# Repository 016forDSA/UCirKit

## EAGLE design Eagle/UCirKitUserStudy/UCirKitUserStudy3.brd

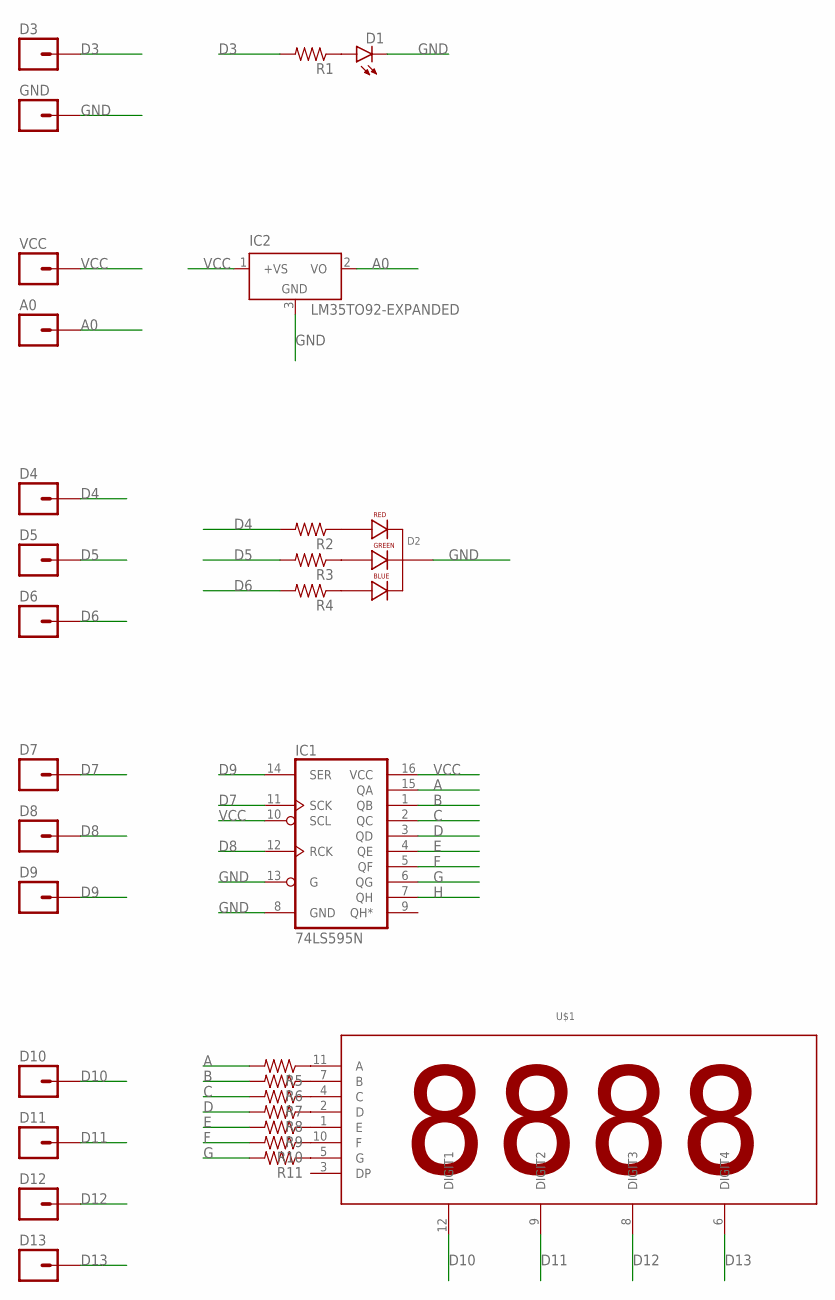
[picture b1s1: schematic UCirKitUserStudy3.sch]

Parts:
A0: M01PTH; 1X01
D1: LEDLED3MM-EXPANDED; LED3MM-EXPANDED
D2: LED-RGB-CC-THRUEXPANDED; LED-RGB-THRU-EXPANDED
D3, D4, D5, D6, D7, D8, D9, D10, D11, D12, D13: M01PTH; 1X01
GND: M01PTH; 1X01
IC1: 74LS595N; DIL16
IC2: LM35TO92-EXPANDED; TO92-EXPANDED
R1, R2, R3, R4, R5, R6, R7, R8, R9, R10, R11: 1KOHM-1/4W-1%(PTH)PTH-EXPANDED; PTH-EXPANDED
U$1: 4DIGIT_SEVEN_SEGMENT4DIGIT_SEVEN_SEGMENT; 4DIGIT_SEVEN_SEGMENT
VCC: M01PTH; 1X01

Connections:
A: IC1.15 (QA), R5.P$2 (2)
A0: A0.1, IC2.2 (VO)
B: IC1.1 (QB), R6.P$2 (2)
C: IC1.2 (QC), R7.P$2 (2)
D: IC1.3 (QD), R8.P$2 (2)
D3: D3.1, R1.P$2 (2)
D4: D4.1, R2.P$2 (2)
D5: D5.1, R3.P$2 (2)
D6: D6.1, R4.P$2 (2)
D7: D7.1, IC1.11 (SCK)
D8: D8.1, IC1.12 (RCK)
D9: D9.1, IC1.14 (SER)
D10: D10.1, U$1.12 (DIGIT1)
D11: D11.1, U$1.9 (DIGIT2)
D12: D12.1, U$1.8 (DIGIT3)
D13: D13.1, U$1.6 (DIGIT4)
E: IC1.4 (QE), R9.P$2 (2)
F: IC1.5 (QF), R10.P$2 (2)
G: IC1.6 (QG), R11.P$2 (2)
GND: D1.K (C), D2.2 (CATHODE), GND.1, IC1.8 (GND), IC1.13 (G), IC2.3 (GND)
H: IC1.7 (QH)
unnamed: D1.A, R1.P$1 (1)
unnamed: D2.1 (RED_CATHODE), R2.P$1 (1)
unnamed: D2.3 (GREEN_CATHODE), R3.P$1 (1)
unnamed: D2.4 (BLUE_CATHODE), R4.P$1 (1)
unnamed: R5.P$1 (1), U$1.11 (A)
unnamed: R6.P$1 (1), U$1.7 (B)
unnamed: R7.P$1 (1), U$1.4 (C)
unnamed: R8.P$1 (1), U$1.2 (D)
unnamed: R9.P$1 (1), U$1.1 (E)
unnamed: R10.P$1 (1), U$1.10 (F)
unnamed: R11.P$1 (1), U$1.5 (G)
VCC: IC1.10 (SCL), IC1.16 (VCC), IC2.1 (+VS), VCC.1

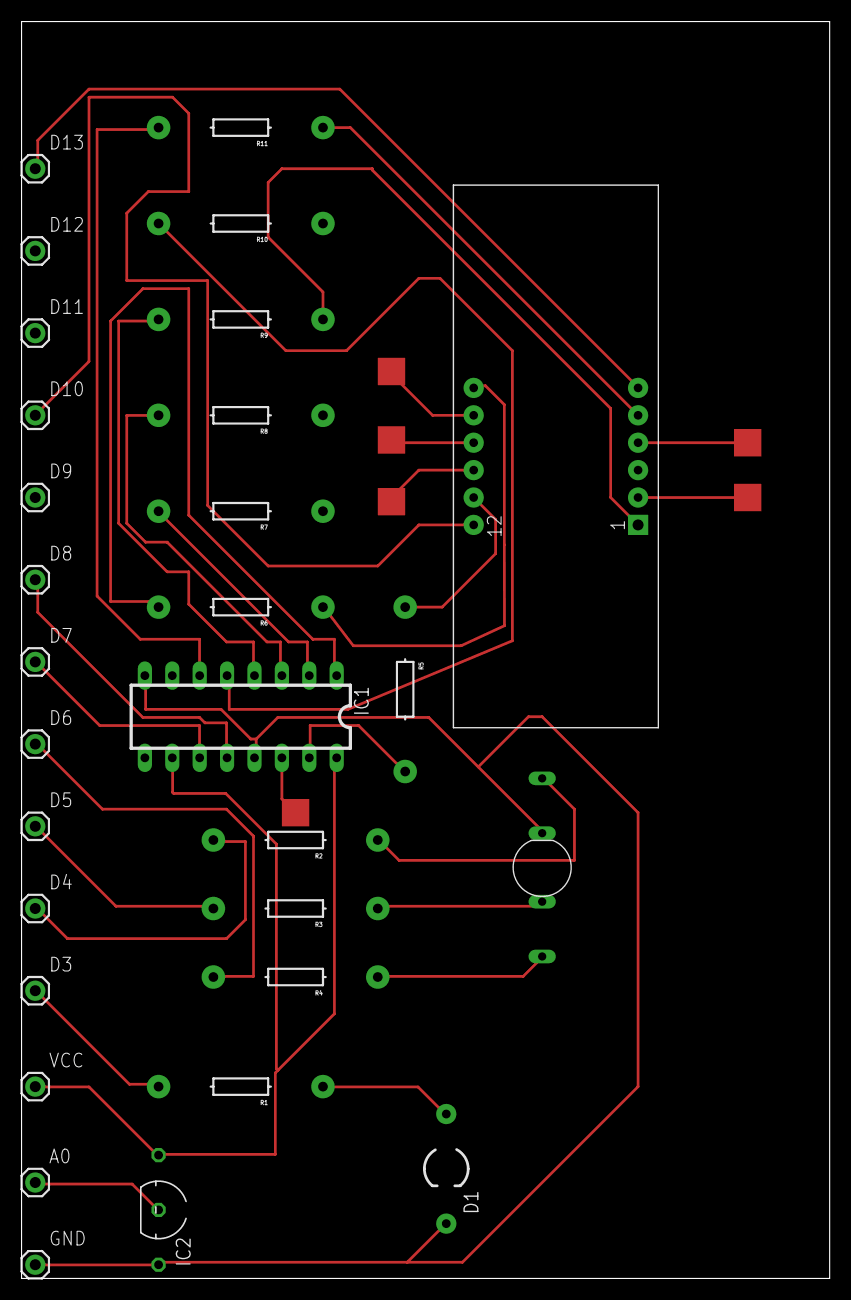
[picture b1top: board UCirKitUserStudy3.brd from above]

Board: 2 copper layers, 74.9 x 116.5 mm, 30 parts (0 on the bottom side), 32 nets.

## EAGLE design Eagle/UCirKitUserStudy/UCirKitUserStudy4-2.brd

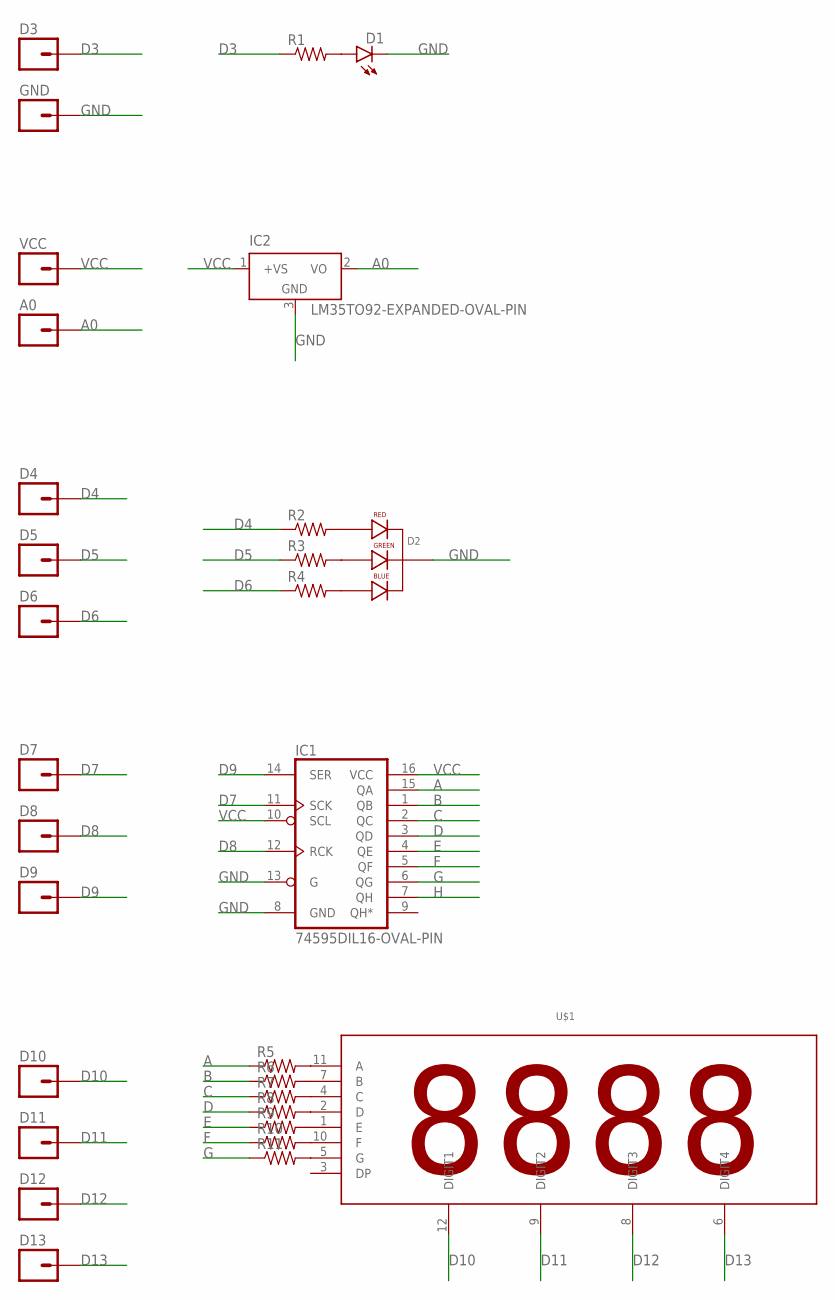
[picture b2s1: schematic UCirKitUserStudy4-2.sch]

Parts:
A0: M01OVAL_PIN; 1X01_OVAL_PIN
D1: LEDLED3MM-EXPANDED-OVAL-PIN; LED3MM-EXPANDED-OVAL-PIN
D2: LED-RGB-CC-THRULED-RGB-THRU-EXPANDED-OVAL-PIN; LED-RGB-THRU-EXPANDED-OVAL-PIN
D3, D4, D5, D6, D7, D8, D9, D10, D11, D12, D13: M01OVAL_PIN; 1X01_OVAL_PIN
GND: M01OVAL_PIN; 1X01_OVAL_PIN
IC1: 74595DIL16-OVAL-PIN; DIL16-OVAL-PIN
IC2: LM35TO92-EXPANDED-OVAL-PIN; TO92-EXPANDED-OVAL-PIN
R1, R2, R3, R4, R5, R6, R7, R8, R9, R10, R11: 1KOHM-1/4W-1%(PTH)PTH-EXPANDED-OVAL-PIN; PTH-EXPANDED-OVAL-PIN
U$1: 4DIGIT_SEVEN_SEGMENT4DIGIT_SEVEN_SEGMENT_OVAL_PIN; 4DIGIT_SEVEN_SEGMENT_OVAL_PIN
VCC: M01OVAL_PIN; 1X01_OVAL_PIN

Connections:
A: IC1.15 (QA), R5.P$1 (1)
A0: A0.1, IC2.2 (VO)
B: IC1.1 (QB), R6.P$1 (1)
C: IC1.2 (QC), R7.P$1 (1)
D: IC1.3 (QD), R8.P$1 (1)
D3: D3.1, R1.P$1 (1)
D4: D4.1, R2.P$1 (1)
D5: D5.1, R3.P$1 (1)
D6: D6.1, R4.P$1 (1)
D7: D7.1, IC1.11 (SCK)
D8: D8.1, IC1.12 (RCK)
D9: D9.1, IC1.14 (SER)
D10: D10.1, U$1.12 (DIGIT1)
D11: D11.1, U$1.9 (DIGIT2)
D12: D12.1, U$1.8 (DIGIT3)
D13: D13.1, U$1.6 (DIGIT4)
E: IC1.4 (QE), R9.P$1 (1)
F: IC1.5 (QF), R10.P$1 (1)
G: IC1.6 (QG), R11.P$1 (1)
GND: D1.K (C), D2.2 (CATHODE), GND.1, IC1.8 (GND), IC1.13 (G), IC2.3 (GND)
H: IC1.7 (QH)
unnamed: D1.A, R1.P$2 (2)
unnamed: D2.1 (RED_CATHODE), R2.P$2 (2)
unnamed: D2.3 (GREEN_CATHODE), R3.P$2 (2)
unnamed: D2.4 (BLUE_CATHODE), R4.P$2 (2)
unnamed: R5.P$2 (2), U$1.11 (A)
unnamed: R6.P$2 (2), U$1.7 (B)
unnamed: R7.P$2 (2), U$1.4 (C)
unnamed: R8.P$2 (2), U$1.2 (D)
unnamed: R9.P$2 (2), U$1.1 (E)
unnamed: R10.P$2 (2), U$1.10 (F)
unnamed: R11.P$2 (2), U$1.5 (G)
VCC: IC1.10 (SCL), IC1.16 (VCC), IC2.1 (+VS), VCC.1

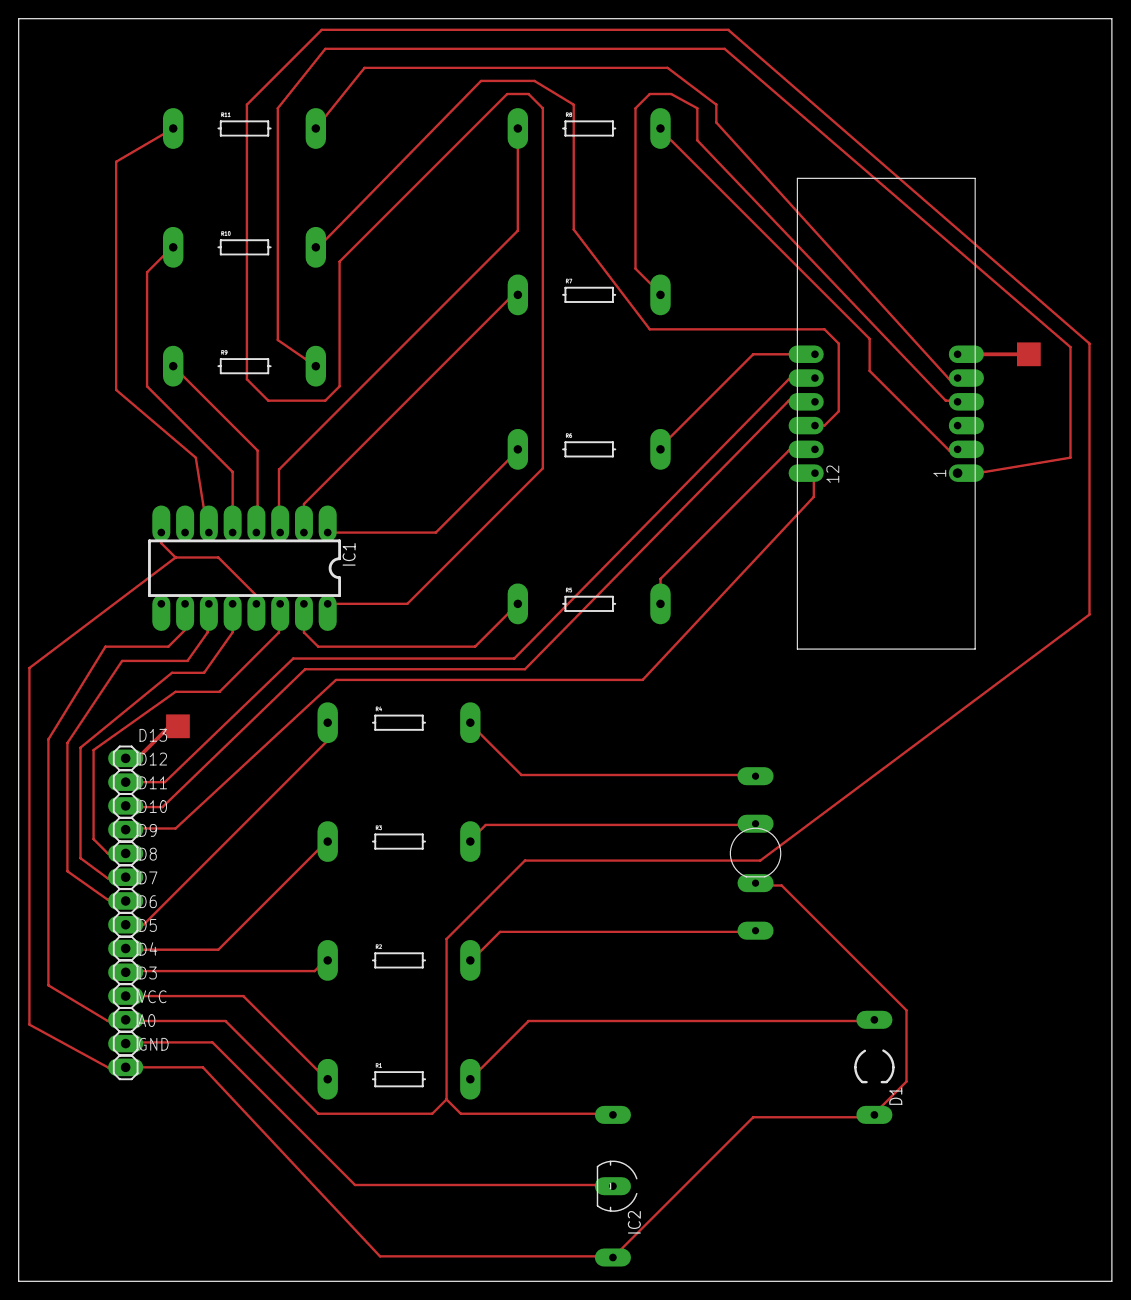
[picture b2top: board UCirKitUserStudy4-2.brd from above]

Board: 2 copper layers, 116.8 x 134.9 mm, 30 parts (0 on the bottom side), 32 nets.

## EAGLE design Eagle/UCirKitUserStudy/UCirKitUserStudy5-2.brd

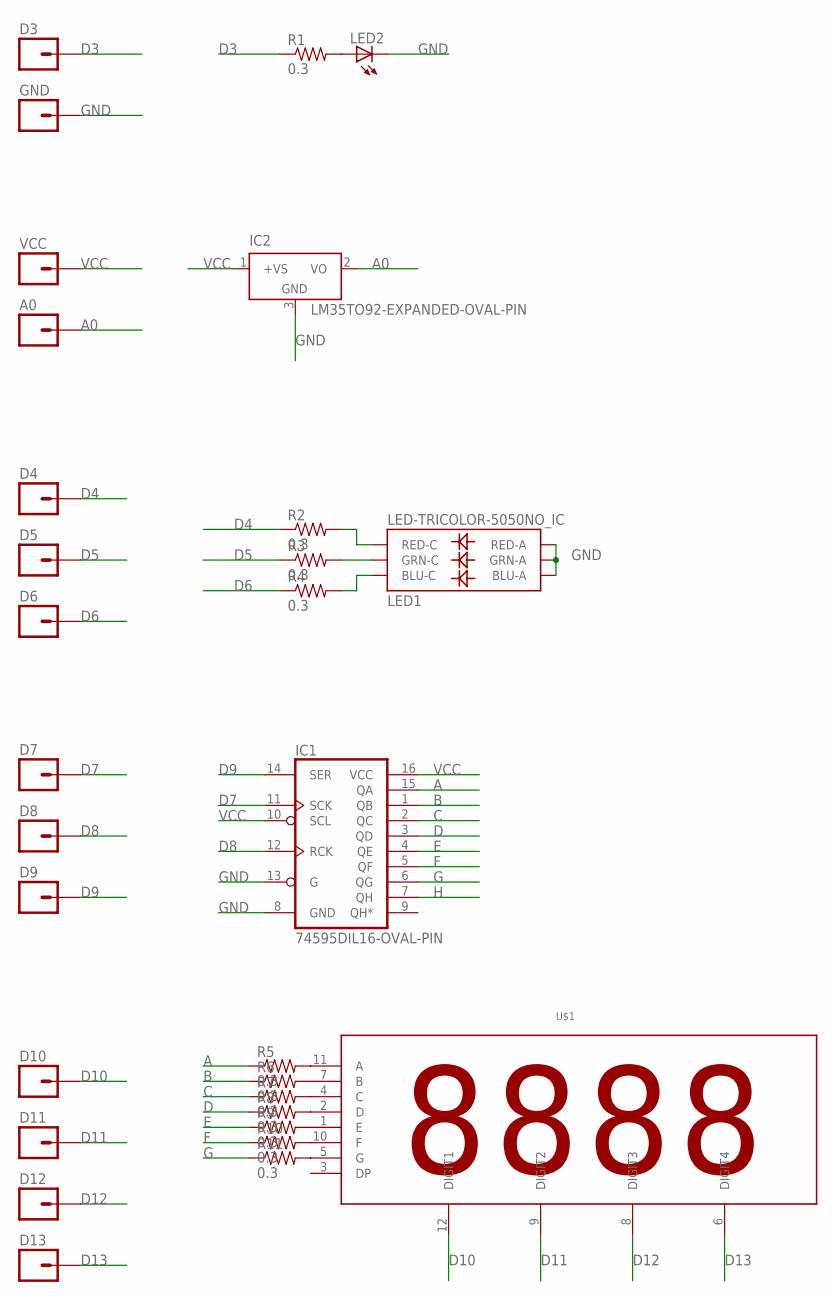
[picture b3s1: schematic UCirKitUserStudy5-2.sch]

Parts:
A0: M01OVAL_PIN; 1X01_OVAL_PIN
D3, D4, D5, D6, D7, D8, D9, D10, D11, D12, D13: M01OVAL_PIN; 1X01_OVAL_PIN
GND: M01OVAL_PIN; 1X01_OVAL_PIN
IC1: 74595DIL16-OVAL-PIN; DIL16-OVAL-PIN
IC2: LM35TO92-EXPANDED-OVAL-PIN; TO92-EXPANDED-OVAL-PIN
LED1: LED-TRICOLOR-5050NO_IC; LED-TRICOLOR-5050
LED2: LEDCHIP-LED0805; CHIP-LED0805
R1, R2, R3, R4, R5, R6, R7, R8, R9, R10, R11: 0.3; 0805
U$1: 4DIGIT_SEVEN_SEGMENT4DIGIT_SEVEN_SEGMENT_OVAL_PIN; 4DIGIT_SEVEN_SEGMENT_OVAL_PIN
VCC: M01OVAL_PIN; 1X01_OVAL_PIN

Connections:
A: IC1.15 (QA), R5.1
A0: A0.1, IC2.2 (VO)
B: IC1.1 (QB), R6.1
C: IC1.2 (QC), R7.1
D: IC1.3 (QD), R8.1
D3: D3.1, R1.1
D4: D4.1, R2.1
D5: D5.1, R3.1
D6: D6.1, R4.1
D7: D7.1, IC1.11 (SCK)
D8: D8.1, IC1.12 (RCK)
D9: D9.1, IC1.14 (SER)
D10: D10.1, U$1.12 (DIGIT1)
D11: D11.1, U$1.9 (DIGIT2)
D12: D12.1, U$1.8 (DIGIT3)
D13: D13.1, U$1.6 (DIGIT4)
E: IC1.4 (QE), R9.1
F: IC1.5 (QF), R10.1
G: IC1.6 (QG), R11.1
GND: GND.1, IC1.8 (GND), IC1.13 (G), IC2.3 (GND), LED1.1 (GRN-A), LED1.2 (RED-A), LED1.3 (BLU-A), LED2.C
H: IC1.7 (QH)
unnamed: R5.2, U$1.11 (A)
unnamed: R6.2, U$1.7 (B)
unnamed: R7.2, U$1.4 (C)
unnamed: R8.2, U$1.2 (D)
unnamed: R9.2, U$1.1 (E)
unnamed: R10.2, U$1.10 (F)
unnamed: R11.2, U$1.5 (G)
unnamed: LED1.5 (RED-C), R2.2
unnamed: LED1.6 (GRN-C), R3.2
unnamed: LED1.4 (BLU-C), R4.2
unnamed: LED2.A, R1.2
VCC: IC1.10 (SCL), IC1.16 (VCC), IC2.1 (+VS), VCC.1

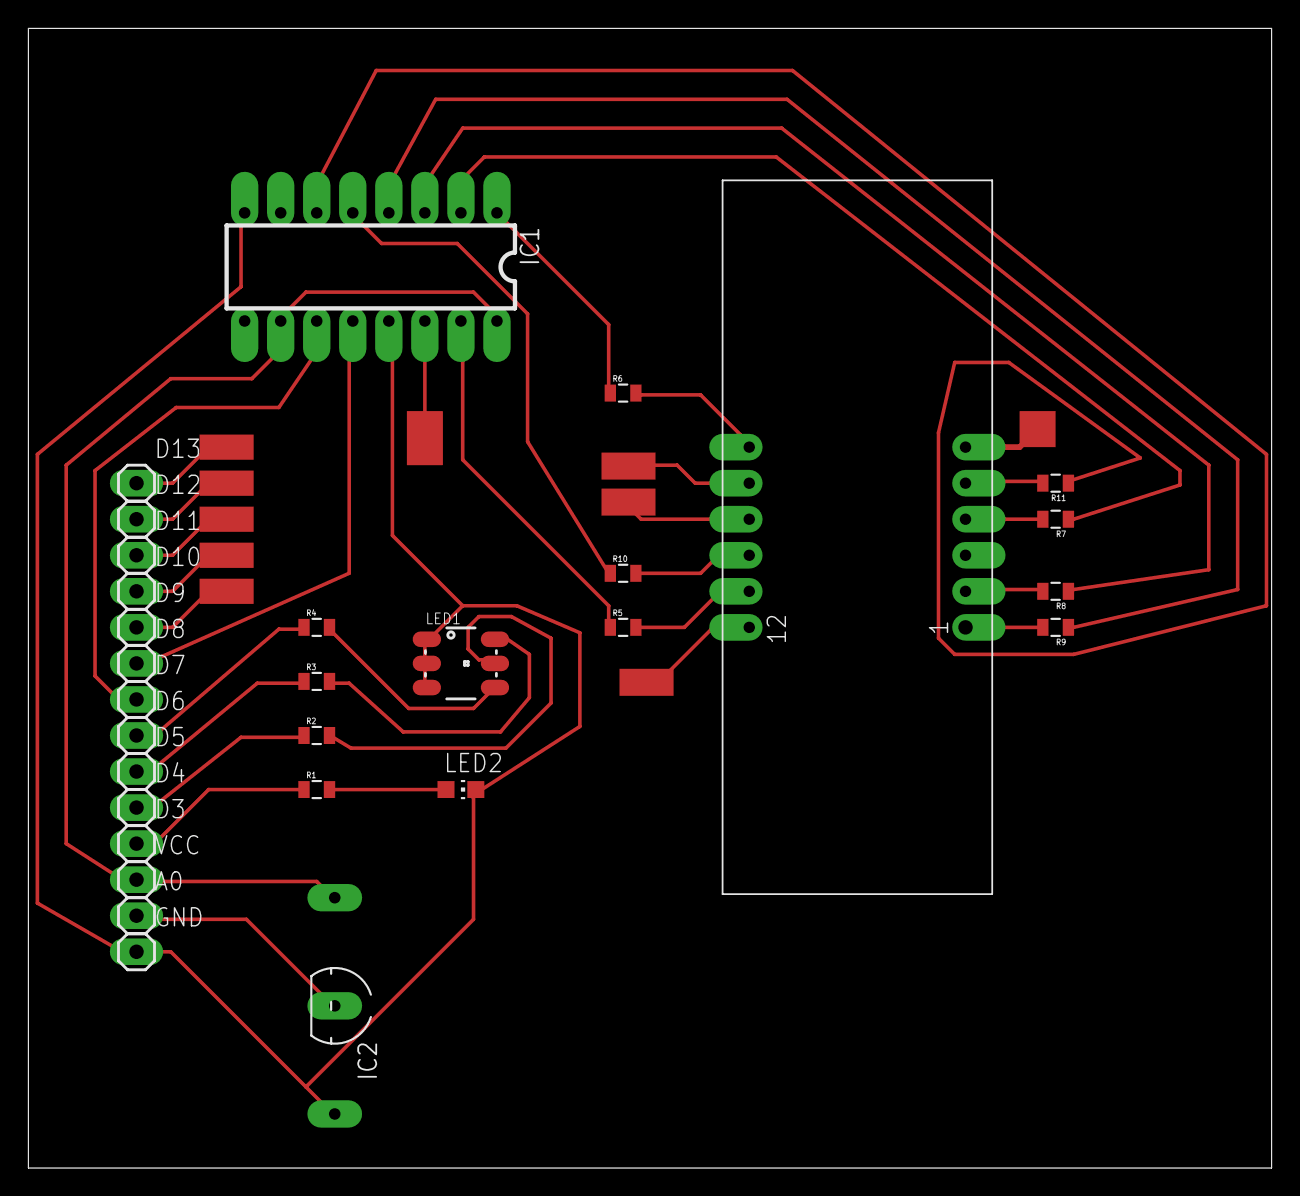
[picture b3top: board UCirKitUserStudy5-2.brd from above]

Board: 2 copper layers, 87.6 x 80.3 mm, 30 parts (0 on the bottom side), 32 nets.

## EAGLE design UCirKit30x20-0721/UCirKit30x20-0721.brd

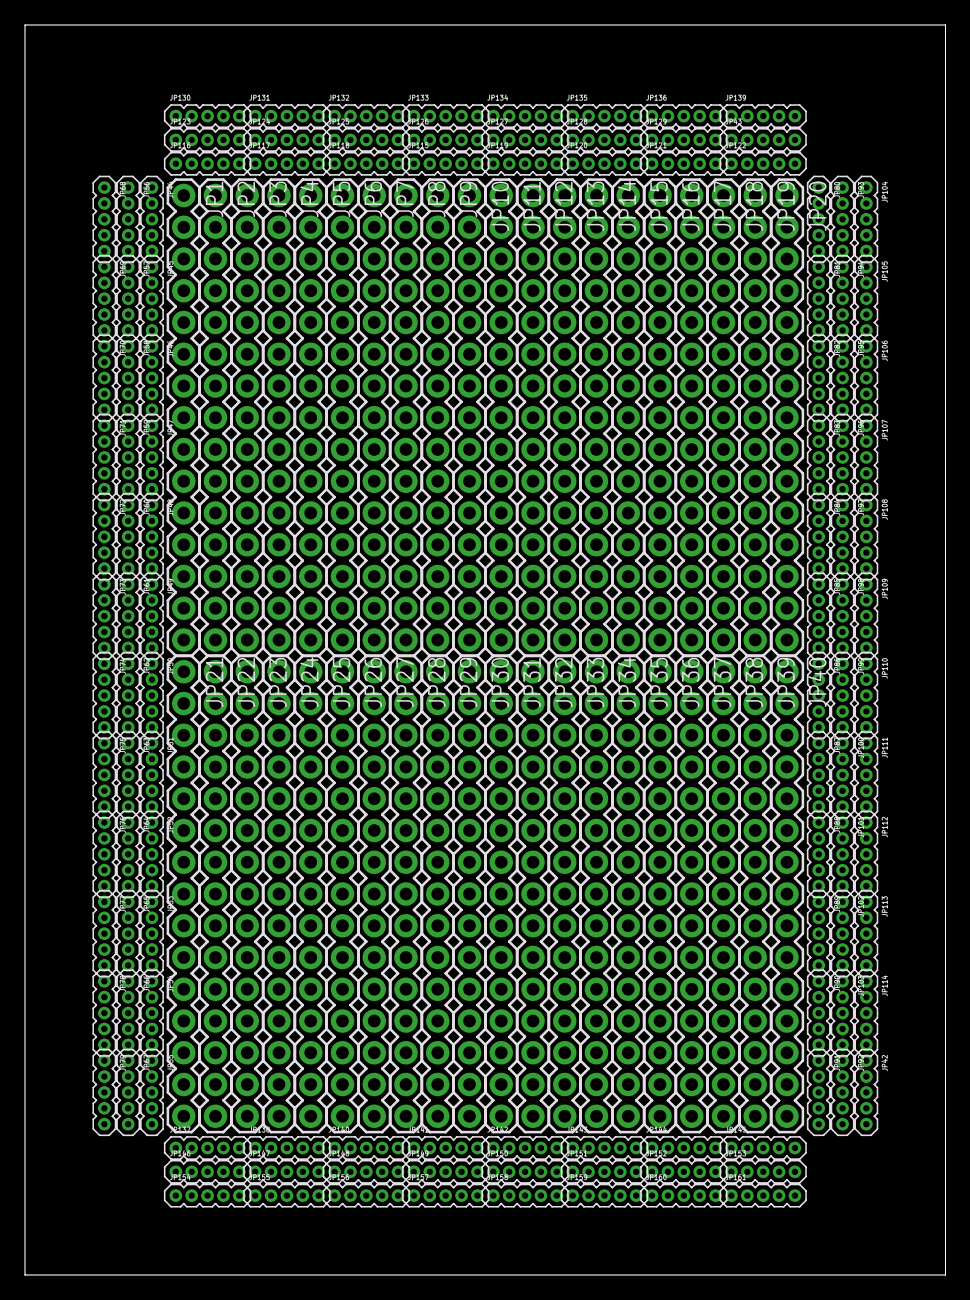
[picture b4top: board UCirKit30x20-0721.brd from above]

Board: 2 copper layers, 73.6 x 100.0 mm, 160 parts (0 on the bottom side), 541 nets, no tracks yet.

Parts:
JP1, JP2, JP3, JP4, JP5, JP6, JP7, JP8, JP9, JP10, JP11, JP12, JP13, JP14, JP15, JP16, JP17, JP18, JP19, JP20, JP21, JP22, JP23, JP24, JP25, JP26, JP27, JP28, JP29, JP30, JP31, JP32, JP33, JP34, JP35, JP36, JP37, JP38, JP39, JP40: 1X15
JP42, JP43, JP44, JP45, JP46, JP47, JP48, JP49, JP50, JP51, JP52, JP53, JP54, JP55, JP56, JP57, JP58, JP59, JP60, JP61, JP62, JP63, JP64, JP65, JP66, JP67, JP68, JP69, JP70, JP71, JP72, JP73, JP74, JP75, JP76, JP77, JP78, JP79, JP80, JP81, JP82, JP83, JP84, JP85, JP86, JP87, JP88, JP89, JP90, JP91, JP92, JP93, JP94, JP95, JP96, JP97, JP98, JP99, JP100, JP101, JP102, JP103, JP104, JP105, JP106, JP107, JP108, JP109, JP110, JP111, JP112, JP113, JP114, JP115, JP116, JP117, JP118, JP119, JP120, JP121, JP122, JP123, JP124, JP125, JP126, JP127, JP128, JP129, JP130, JP131, JP132, JP133, JP134, JP135, JP136, JP137, JP138, JP139, JP140, JP141, JP142, JP143, JP144, JP145, JP146, JP147, JP148, JP149, JP150, JP151, JP152, JP153, JP154, JP155, JP156, JP157, JP158, JP159, JP160, JP161: 1X05-1.27MM

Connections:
1-1: JP1.1, JP43.1
1-2: JP1.2, JP43.2
1-3: JP1.3, JP43.3
1-4: JP1.4, JP43.4
1-5: JP1.5, JP43.5
1-6: JP1.6, JP42.1
1-7: JP1.7, JP42.2
1-8: JP1.8, JP42.3
1-9: JP1.9, JP42.4
1-10: JP1.10, JP42.5
1-11: JP1.11, JP161.1
1-12: JP1.12, JP161.2
1-13: JP1.13, JP161.3
1-14: JP1.14, JP161.4
1-15: JP1.15, JP161.5
2-1: JP2.1, JP46.1
2-2: JP2.2, JP46.2
2-3: JP2.3, JP46.3
2-4: JP2.4, JP46.4
2-5: JP2.5, JP46.5
2-6: JP2.6, JP45.1
2-7: JP2.7, JP45.2
2-8: JP2.8, JP45.3
2-9: JP2.9, JP45.4
2-10: JP2.10, JP45.5
2-11: JP2.11, JP44.1
2-12: JP2.12, JP44.2
2-13: JP2.13, JP44.3
2-14: JP2.14, JP44.4
2-15: JP2.15, JP44.5
3-1: JP3.1, JP49.1
3-2: JP3.2, JP49.2
3-3: JP3.3, JP49.3
3-4: JP3.4, JP49.4
3-5: JP3.5, JP49.5
3-6: JP3.6, JP48.1
3-7: JP3.7, JP48.2
3-8: JP3.8, JP48.3
3-9: JP3.9, JP48.4
3-10: JP3.10, JP48.5
3-11: JP3.11, JP47.1
3-12: JP3.12, JP47.2
3-13: JP3.13, JP47.3
3-14: JP3.14, JP47.4
3-15: JP3.15, JP47.5
4-1: JP4.1, JP52.1
4-2: JP4.2, JP52.2
4-3: JP4.3, JP52.3
4-4: JP4.4, JP52.4
4-5: JP4.5, JP52.5
4-6: JP4.6, JP51.1
4-7: JP4.7, JP51.2
4-8: JP4.8, JP51.3
4-9: JP4.9, JP51.4
4-10: JP4.10, JP51.5
4-11: JP4.11, JP50.1
4-12: JP4.12, JP50.2
4-13: JP4.13, JP50.3
4-14: JP4.14, JP50.4
4-15: JP4.15, JP50.5
5-1: JP5.1, JP55.1
5-2: JP5.2, JP55.2
5-3: JP5.3, JP55.3
5-4: JP5.4, JP55.4
5-5: JP5.5, JP55.5
5-6: JP5.6, JP54.1
5-7: JP5.7, JP54.2
5-8: JP5.8, JP54.3
5-9: JP5.9, JP54.4
5-10: JP5.10, JP54.5
5-11: JP5.11, JP53.1
5-12: JP5.12, JP53.2
5-13: JP5.13, JP53.3
5-14: JP5.14, JP53.4
5-15: JP5.15, JP53.5
6-1: JP6.1, JP58.1
6-2: JP6.2, JP58.2
6-3: JP6.3, JP58.3
6-4: JP6.4, JP58.4
6-5: JP6.5, JP58.5
6-6: JP6.6, JP57.1
6-7: JP6.7, JP57.2
6-8: JP6.8, JP57.3
6-9: JP6.9, JP57.4
6-10: JP6.10, JP57.5
6-11: JP6.11, JP56.1
6-12: JP6.12, JP56.2
6-13: JP6.13, JP56.3
6-14: JP6.14, JP56.4
6-15: JP6.15, JP56.5
7-1: JP7.1, JP61.1
7-2: JP7.2, JP61.2
7-3: JP7.3, JP61.3
7-4: JP7.4, JP61.4
7-5: JP7.5, JP61.5
7-6: JP7.6, JP60.1
7-7: JP7.7, JP60.2
7-8: JP7.8, JP60.3
7-9: JP7.9, JP60.4
7-10: JP7.10, JP60.5
7-11: JP7.11, JP59.1
7-12: JP7.12, JP59.2
7-13: JP7.13, JP59.3
7-14: JP7.14, JP59.4
7-15: JP7.15, JP59.5
8-1: JP8.1, JP64.1
8-2: JP8.2, JP64.2
8-3: JP8.3, JP64.3
8-4: JP8.4, JP64.4
8-5: JP8.5, JP64.5
8-6: JP8.6, JP63.1
8-7: JP8.7, JP63.2
8-8: JP8.8, JP63.3
8-9: JP8.9, JP63.4
8-10: JP8.10, JP63.5
8-11: JP8.11, JP62.1
8-12: JP8.12, JP62.2
8-13: JP8.13, JP62.3
8-14: JP8.14, JP62.4
8-15: JP8.15, JP62.5
9-1: JP9.1, JP67.1
9-2: JP9.2, JP67.2
9-3: JP9.3, JP67.3
9-4: JP9.4, JP67.4
9-5: JP9.5, JP67.5
9-6: JP9.6, JP66.1
9-7: JP9.7, JP66.2
9-8: JP9.8, JP66.3
9-9: JP9.9, JP66.4
9-10: JP9.10, JP66.5
9-11: JP9.11, JP65.1
9-12: JP9.12, JP65.2
9-13: JP9.13, JP65.3
9-14: JP9.14, JP65.4
9-15: JP9.15, JP65.5
10-1: JP10.1, JP70.1
10-2: JP10.2, JP70.2
10-3: JP10.3, JP70.3
10-4: JP10.4, JP70.4
10-5: JP10.5, JP70.5
10-6: JP10.6, JP69.1
10-7: JP10.7, JP69.2
10-8: JP10.8, JP69.3
10-9: JP10.9, JP69.4
10-10: JP10.10, JP69.5
10-11: JP10.11, JP68.1
10-12: JP10.12, JP68.2
10-13: JP10.13, JP68.3
10-14: JP10.14, JP68.4
10-15: JP10.15, JP68.5
11-1: JP11.1, JP73.1
11-2: JP11.2, JP73.2
11-3: JP11.3, JP73.3
11-4: JP11.4, JP73.4
11-5: JP11.5, JP73.5
11-6: JP11.6, JP72.1
11-7: JP11.7, JP72.2
11-8: JP11.8, JP72.3
11-9: JP11.9, JP72.4
11-10: JP11.10, JP72.5
11-11: JP11.11, JP71.1
11-12: JP11.12, JP71.2
11-13: JP11.13, JP71.3
11-14: JP11.14, JP71.4
11-15: JP11.15, JP71.5
12-15: JP12.15, JP74.5
14-15: JP14.15, JP80.5
15-2: JP15.2, JP85.2
15-14: JP15.14, JP113.4
15-15: JP15.15, JP83.5, JP113.5
16-1: JP16.1, JP88.1
16-2: JP16.2, JP88.2
16-3: JP16.3, JP88.3
16-4: JP16.4, JP88.4
16-5: JP16.5, JP88.5
16-6: JP16.6, JP87.1
16-7: JP16.7, JP87.2
16-8: JP16.8, JP87.3
16-9: JP16.9, JP87.4
16-10: JP16.10, JP87.5
16-11: JP16.11, JP86.1
16-12: JP16.12, JP86.2
16-13: JP16.13, JP86.3
16-14: JP16.14, JP86.4
16-15: JP16.15, JP86.5
17-1: JP17.1, JP91.1
17-2: JP17.2, JP91.2
17-3: JP17.3, JP91.3
17-4: JP17.4, JP91.4
17-5: JP17.5, JP91.5
17-6: JP17.6, JP90.1
17-7: JP17.7, JP90.2
17-8: JP17.8, JP90.3
17-9: JP17.9, JP90.4
17-10: JP17.10, JP90.5
17-11: JP17.11, JP89.1
17-12: JP17.12, JP89.2
17-13: JP17.13, JP89.3
17-14: JP17.14, JP89.4
17-15: JP17.15, JP89.5
18-1: JP18.1, JP94.1
18-2: JP18.2, JP94.2
18-3: JP18.3, JP94.3
18-4: JP18.4, JP94.4
18-5: JP18.5, JP94.5
18-6: JP18.6, JP93.1
18-7: JP18.7, JP93.2
18-8: JP18.8, JP93.3
18-9: JP18.9, JP93.4
18-10: JP18.10, JP93.5
18-11: JP18.11, JP92.1
18-12: JP18.12, JP92.2
18-13: JP18.13, JP92.3
18-14: JP18.14, JP92.4
18-15: JP18.15, JP92.5
19-1: JP19.1, JP97.1
19-2: JP19.2, JP97.2
19-3: JP19.3, JP97.3
19-4: JP19.4, JP97.4
19-5: JP19.5, JP97.5
19-6: JP19.6, JP96.1
19-7: JP19.7, JP96.2
19-8: JP19.8, JP96.3
19-9: JP19.9, JP96.4
19-10: JP19.10, JP96.5
19-11: JP19.11, JP95.1
19-12: JP19.12, JP95.2
19-13: JP19.13, JP95.3
19-14: JP19.14, JP95.4
19-15: JP19.15, JP95.5
20-1: JP20.1, JP100.1
20-2: JP20.2, JP100.2
20-3: JP20.3, JP100.3
20-4: JP20.4, JP100.4
20-5: JP20.5, JP100.5
20-6: JP20.6, JP99.1
20-7: JP20.7, JP99.2
20-8: JP20.8, JP99.3
20-9: JP20.9, JP99.4
20-10: JP20.10, JP99.5
20-11: JP20.11, JP98.1
20-12: JP20.12, JP98.2
20-13: JP20.13, JP98.3
20-14: JP20.14, JP98.4
20-15: JP20.15, JP98.5
21-1: JP21.1, JP103.1
21-2: JP21.2, JP103.2
21-3: JP21.3, JP103.3
21-4: JP21.4, JP103.4
21-5: JP21.5, JP103.5
21-6: JP21.6, JP102.1
21-7: JP21.7, JP102.2
21-8: JP21.8, JP102.3
21-9: JP21.9, JP102.4
21-10: JP21.10, JP102.5
21-11: JP21.11, JP101.1
21-12: JP21.12, JP101.2
21-13: JP21.13, JP101.3
21-14: JP21.14, JP101.4
21-15: JP21.15, JP101.5
22-1: JP22.1, JP106.1
22-2: JP22.2, JP106.2
22-3: JP22.3, JP106.3
22-4: JP22.4, JP106.4
22-5: JP22.5, JP106.5
22-6: JP22.6, JP105.1
22-7: JP22.7, JP105.2
22-8: JP22.8, JP105.3
22-9: JP22.9, JP105.4
22-10: JP22.10, JP105.5
22-11: JP22.11, JP104.1
22-12: JP22.12, JP104.2
22-13: JP22.13, JP104.3
22-14: JP22.14, JP104.4
22-15: JP22.15, JP104.5
23-1: JP23.1, JP109.1
23-2: JP23.2, JP109.2
23-3: JP23.3, JP109.3
23-4: JP23.4, JP109.4
23-5: JP23.5, JP109.5
23-6: JP23.6, JP108.1
23-7: JP23.7, JP108.2
23-8: JP23.8, JP108.3
23-9: JP23.9, JP108.4
23-10: JP23.10, JP108.5
23-11: JP23.11, JP107.1
23-12: JP23.12, JP107.2
23-13: JP23.13, JP107.3
23-14: JP23.14, JP107.4
23-15: JP23.15, JP107.5
24-1: JP24.1, JP112.1
24-2: JP24.2, JP112.2
24-3: JP24.3, JP112.3
24-4: JP24.4, JP112.4
24-5: JP24.5, JP112.5
24-6: JP24.6, JP111.1
24-7: JP24.7, JP111.2
24-8: JP24.8, JP111.3
24-9: JP24.9, JP111.4
24-10: JP24.10, JP111.5
24-11: JP24.11, JP110.1
24-12: JP24.12, JP110.2
24-13: JP24.13, JP110.3
24-14: JP24.14, JP110.4
24-15: JP24.15, JP110.5
25-1: JP25.1, JP115.1
25-2: JP25.2, JP115.2
25-3: JP25.3, JP115.3
25-4: JP25.4, JP115.4
25-5: JP25.5, JP115.5
25-6: JP25.6, JP114.1
25-7: JP25.7, JP114.2
25-8: JP25.8, JP114.3
25-9: JP25.9, JP114.4
25-10: JP25.10, JP114.5
25-11: JP25.11, JP113.1
25-12: JP25.12, JP113.2
25-13: JP25.13, JP113.3
26-1: JP26.1, JP118.1
26-2: JP26.2, JP118.2
26-3: JP26.3, JP118.3
26-4: JP26.4, JP118.4
26-5: JP26.5, JP118.5
26-6: JP26.6, JP117.1
26-7: JP26.7, JP117.2
26-8: JP26.8, JP117.3
26-9: JP26.9, JP117.4
26-10: JP26.10, JP117.5
26-11: JP26.11, JP116.1
26-12: JP26.12, JP116.2
26-13: JP26.13, JP116.3
26-14: JP26.14, JP116.4
26-15: JP26.15, JP116.5
27-1: JP27.1, JP121.1
27-2: JP27.2, JP121.2
27-3: JP27.3, JP121.3
27-4: JP27.4, JP121.4
27-5: JP27.5, JP121.5
27-6: JP27.6, JP120.1
27-7: JP27.7, JP120.2
27-8: JP27.8, JP120.3
27-9: JP27.9, JP120.4
27-10: JP27.10, JP120.5
27-11: JP27.11, JP119.1
27-12: JP27.12, JP119.2
27-13: JP27.13, JP119.3
27-14: JP27.14, JP119.4
27-15: JP27.15, JP119.5
28-1: JP28.1, JP124.1
28-2: JP28.2, JP124.2
28-3: JP28.3, JP124.3
28-4: JP28.4, JP124.4
28-5: JP28.5, JP124.5
28-6: JP28.6, JP123.1
28-7: JP28.7, JP123.2
28-8: JP28.8, JP123.3
28-9: JP28.9, JP123.4
28-10: JP28.10, JP123.5
28-11: JP28.11, JP122.1
28-12: JP28.12, JP122.2
28-13: JP28.13, JP122.3
28-14: JP28.14, JP122.4
28-15: JP28.15, JP122.5
29-1: JP29.1, JP127.1
29-2: JP29.2, JP127.2
29-3: JP29.3, JP127.3
29-4: JP29.4, JP127.4
29-5: JP29.5, JP127.5
29-6: JP29.6, JP126.1
29-7: JP29.7, JP126.2
29-8: JP29.8, JP126.3
29-9: JP29.9, JP126.4
29-10: JP29.10, JP126.5
29-11: JP29.11, JP125.1
29-12: JP29.12, JP125.2
29-13: JP29.13, JP125.3
29-14: JP29.14, JP125.4
29-15: JP29.15, JP125.5
30-1: JP30.1, JP130.1
30-2: JP30.2, JP130.2
30-3: JP30.3, JP130.3
30-4: JP30.4, JP130.4
30-5: JP30.5, JP130.5
30-6: JP30.6, JP129.1
30-7: JP30.7, JP129.2
30-8: JP30.8, JP129.3
30-9: JP30.9, JP129.4
30-10: JP30.10, JP129.5
30-11: JP30.11, JP128.1
30-12: JP30.12, JP128.2
30-13: JP30.13, JP128.3
30-14: JP30.14, JP128.4
30-15: JP30.15, JP128.5
31-1: JP31.1, JP133.1
31-2: JP31.2, JP133.2
31-3: JP31.3, JP133.3
31-4: JP31.4, JP133.4
31-5: JP31.5, JP133.5
31-6: JP31.6, JP132.1
31-7: JP31.7, JP132.2
31-8: JP31.8, JP132.3
31-9: JP31.9, JP132.4
31-10: JP31.10, JP132.5
31-11: JP31.11, JP131.1
31-12: JP31.12, JP131.2
31-13: JP31.13, JP131.3
31-14: JP31.14, JP131.4
31-15: JP31.15, JP131.5
32-1: JP32.1, JP136.1
32-2: JP32.2, JP136.2
32-3: JP32.3, JP136.3
32-4: JP32.4, JP136.4
32-5: JP32.5, JP136.5
32-6: JP32.6, JP135.1
32-7: JP32.7, JP135.2
32-8: JP32.8, JP135.3
32-9: JP32.9, JP135.4
32-10: JP32.10, JP135.5
32-11: JP32.11, JP134.1
32-12: JP32.12, JP134.2
32-13: JP32.13, JP134.3
32-14: JP32.14, JP134.4
32-15: JP32.15, JP134.5
33-1: JP33.1, JP139.1
33-2: JP33.2, JP139.2
33-3: JP33.3, JP139.3
33-4: JP33.4, JP139.4
33-5: JP33.5, JP139.5
33-6: JP33.6, JP138.1
33-7: JP33.7, JP138.2
33-8: JP33.8, JP138.3
33-9: JP33.9, JP138.4
33-10: JP33.10, JP138.5
33-11: JP33.11, JP137.1
33-12: JP33.12, JP137.2
33-13: JP33.13, JP137.3
33-14: JP33.14, JP137.4
33-15: JP33.15, JP137.5
34-1: JP34.1, JP142.1
34-2: JP34.2, JP142.2
34-3: JP34.3, JP142.3
34-4: JP34.4, JP142.4
34-5: JP34.5, JP142.5
34-6: JP34.6, JP141.1
34-7: JP34.7, JP141.2
34-8: JP34.8, JP141.3
34-9: JP34.9, JP141.4
34-10: JP34.10, JP141.5
34-11: JP34.11, JP140.1
34-12: JP34.12, JP140.2
34-13: JP34.13, JP140.3
34-14: JP34.14, JP140.4
34-15: JP34.15, JP140.5
35-1: JP35.1, JP145.1
35-2: JP35.2, JP145.2
35-3: JP35.3, JP145.3
35-4: JP35.4, JP145.4
35-5: JP35.5, JP145.5
35-6: JP35.6, JP144.1
35-7: JP35.7, JP144.2
35-8: JP35.8, JP144.3
35-9: JP35.9, JP144.4
35-10: JP35.10, JP144.5
35-11: JP35.11, JP143.1
35-12: JP35.12, JP143.2
35-13: JP35.13, JP143.3
35-14: JP35.14, JP143.4
35-15: JP35.15, JP143.5
36-1: JP36.1, JP148.1
36-2: JP36.2, JP148.2
36-3: JP36.3, JP148.3
36-4: JP36.4, JP148.4
36-5: JP36.5, JP147.1, JP148.5
36-7: JP36.7, JP147.2
36-8: JP36.8, JP147.3
36-9: JP36.9, JP147.4
36-10: JP36.10, JP147.5
36-11: JP36.11, JP146.1
36-12: JP36.12, JP146.2
36-13: JP36.13, JP146.3
36-14: JP36.14, JP146.4
36-15: JP36.15, JP146.5
37-1: JP37.1, JP151.1
37-2: JP37.2, JP151.2
37-3: JP37.3, JP151.3
37-4: JP37.4, JP151.4
37-5: JP37.5, JP151.5
37-6: JP37.6, JP150.1
37-7: JP37.7, JP150.2
37-8: JP37.8, JP150.3
37-9: JP37.9, JP150.4
37-10: JP37.10, JP150.5
37-11: JP37.11, JP149.1
37-12: JP37.12, JP149.2
37-13: JP37.13, JP149.3
37-14: JP37.14, JP149.4
37-15: JP37.15, JP149.5
38-1: JP38.1, JP154.1
38-2: JP38.2, JP154.2
38-3: JP38.3, JP154.3
38-4: JP38.4, JP154.4
38-5: JP38.5, JP154.5
38-6: JP38.6, JP153.1
38-7: JP38.7, JP153.2
38-8: JP38.8, JP153.3
38-9: JP38.9, JP153.4
38-10: JP38.10, JP153.5
38-11: JP38.11, JP152.1
38-12: JP38.12, JP152.2
38-13: JP38.13, JP152.3
38-14: JP38.14, JP152.4
38-15: JP38.15, JP152.5
39-1: JP39.1, JP157.1
39-2: JP39.2, JP157.2
39-3: JP39.3, JP157.3
39-4: JP39.4, JP157.4
39-5: JP39.5, JP157.5
39-6: JP39.6, JP156.1
39-7: JP39.7, JP156.2
39-8: JP39.8, JP156.3
39-9: JP39.9, JP156.4
39-10: JP39.10, JP156.5
39-11: JP39.11, JP155.1
39-12: JP39.12, JP155.2
39-13: JP39.13, JP155.3
39-14: JP39.14, JP155.4
39-15: JP39.15, JP155.5
40-2: JP40.2, JP160.2
40-3: JP40.3, JP160.3
40-4: JP40.4, JP160.4
40-5: JP40.5, JP160.5
40-6: JP40.6, JP159.1
40-7: JP40.7, JP159.2
40-8: JP40.8, JP159.3
40-9: JP40.9, JP159.4
40-10: JP40.10, JP159.5
40-11: JP40.11, JP158.1
40-12: JP40.12, JP158.2
40-13: JP40.13, JP158.3
40-14: JP40.14, JP158.4
40-15: JP40.15, JP158.5

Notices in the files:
parts and their libraries:
SparkFun-Resistors: Licensing: Creative Commons ShareAlike 4.0 International - https://creativecommons.org/licenses/by-sa/4.0
